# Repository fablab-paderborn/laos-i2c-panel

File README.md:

# laos-i2c-panel
This is an rebuild of the LAOS I2C Panel v0.4, optimized for single-sided assembly and cnc milled production.

The original pcb is published at
  https://github.com/LaosLaser/AddOns/tree/master/i2c-panel/pcb-0.4
and designed with KiCAD.

This version is redesigned with EAGLE and optimized for milled production.

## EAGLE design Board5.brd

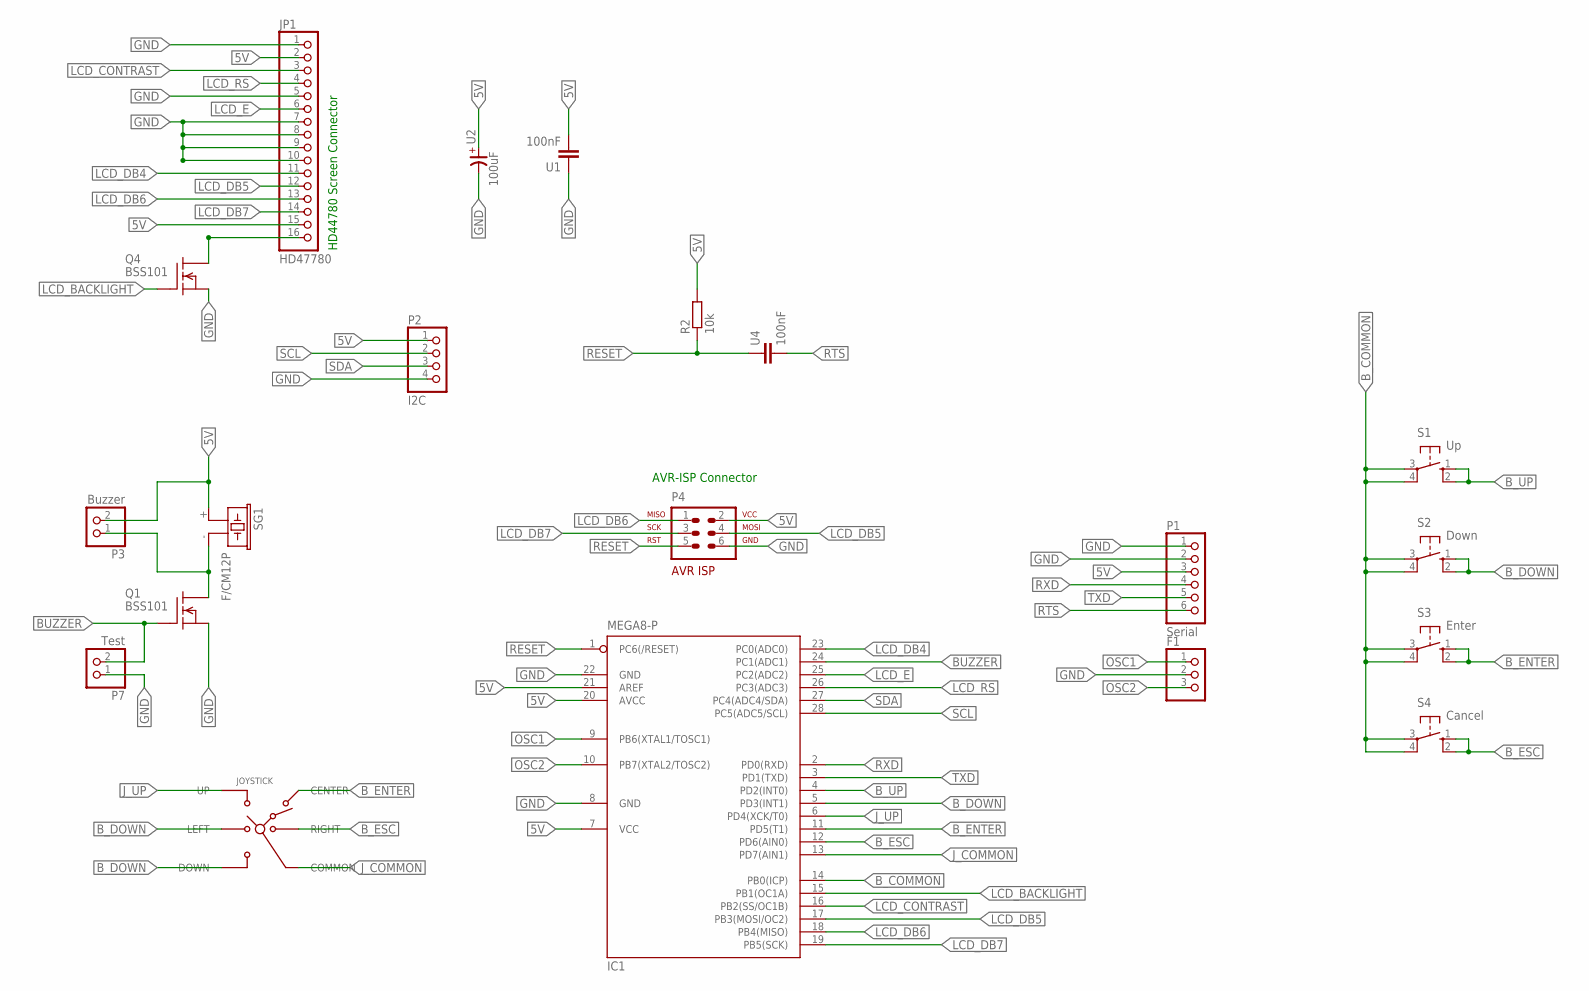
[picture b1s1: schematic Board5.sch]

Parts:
F1: PINHD-1X3; 1X03
IC1: MEGA8-P; DIL28-3
JOYSTICK: SKQUAAA010; SKQU
JP1: HD47780; 1X16
P1: Serial; 1X06
P2: I2C; 1X04
P3: Buzzer; 1X02
P4: ISP_WANNENBUCHSE; ML6
P7: Test; 1X02
Q1, Q4: BSS101; TO92
R2: 10k; 0207/10
S1: Up; B3F-40XX
S2: Down; B3F-40XX
S3: Enter; B3F-40XX
S4: Cancel; B3F-40XX
SG1: F/CM12P
U1, U4: 100nF; C050-024X044
U2: 100uF; E-020X050

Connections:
5V: IC1.7 (VCC), IC1.20 (AVCC), IC1.21 (AREF), JP1.2, JP1.15, P1.3, P2.1, P3.2, P4.2 (VCC), R2.2, SG1.+ (1), U1.2, U2.+
BUZZER: IC1.24 (PC1(ADC1)), P7.2, Q1.2 (G)
B_COMMON: IC1.14 (PB0(ICP)), S1.3, S1.4 (P1), S2.3, S2.4 (P1), S3.3, S3.4 (P1), S4.3, S4.4 (P1)
B_DOWN: IC1.5 (PD3(INT1)), JOYSTICK.DOWN, JOYSTICK.LEFT, S2.1 (S), S2.2 (S1)
B_ENTER: IC1.11 (PD5(T1)), JOYSTICK.CENTER, S3.1 (S), S3.2 (S1)
B_ESC: IC1.12 (PD6(AIN0)), JOYSTICK.RIGHT, S4.1 (S), S4.2 (S1)
B_UP: IC1.4 (PD2(INT0)), S1.1 (S), S1.2 (S1)
GND: F1.2, IC1.8 (GND), IC1.22 (GND), JP1.1, JP1.5, JP1.7, JP1.8, JP1.9, JP1.10, P1.1, P1.2, P2.4, P4.6 (GND), P7.1, Q1.1 (S), Q4.1 (S), U1.1, U2.-
J_COMMON: IC1.13 (PD7(AIN1)), JOYSTICK.COMMON
J_UP: IC1.6 (PD4(XCK/T0)), JOYSTICK.UP
LCD_BACKLIGHT: IC1.15 (PB1(OC1A)), Q4.2 (G)
LCD_CONTRAST: IC1.16 (PB2(SS/OC1B)), JP1.3
LCD_DB4: IC1.23 (PC0(ADC0)), JP1.11
LCD_DB5: IC1.17 (PB3(MOSI/OC2)), JP1.12, P4.4 (MOSI)
LCD_DB6: IC1.18 (PB4(MISO)), JP1.13, P4.1 (MISO)
LCD_DB7: IC1.19 (PB5(SCK)), JP1.14, P4.3 (SCK)
LCD_E: IC1.25 (PC2(ADC2)), JP1.6
LCD_RS: IC1.26 (PC3(ADC3)), JP1.4
unnamed: JP1.16, Q4.3 (D)
unnamed: P3.1, Q1.3 (D), SG1.- (2)
OSC1: F1.1, IC1.9 (PB6(XTAL1/TOSC1))
OSC2: F1.3, IC1.10 (PB7(XTAL2/TOSC2))
RESET: IC1.1 (PC6(/RESET)), P4.5 (RST), R2.1, U4.1
RTS: P1.6, U4.2
RXD: IC1.2 (PD0(RXD)), P1.4
SCL: IC1.28 (PC5(ADC5/SCL)), P2.2
SDA: IC1.27 (PC4(ADC4/SDA)), P2.3
TXD: IC1.3 (PD1(TXD)), P1.5

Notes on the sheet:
AVR-ISP Connector
HD44780 Screen Connector

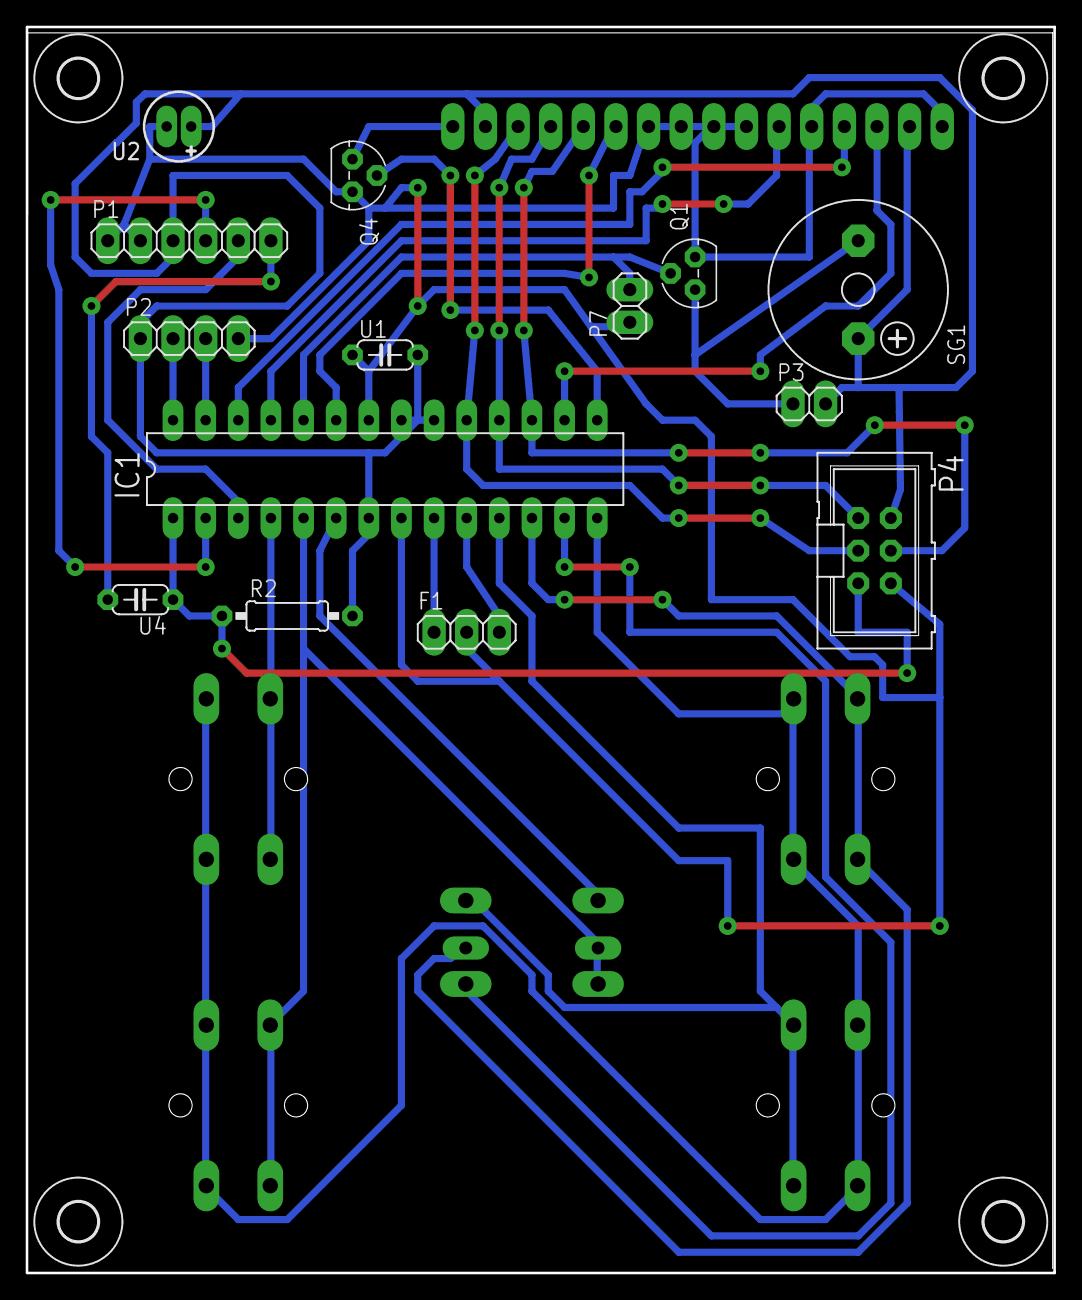
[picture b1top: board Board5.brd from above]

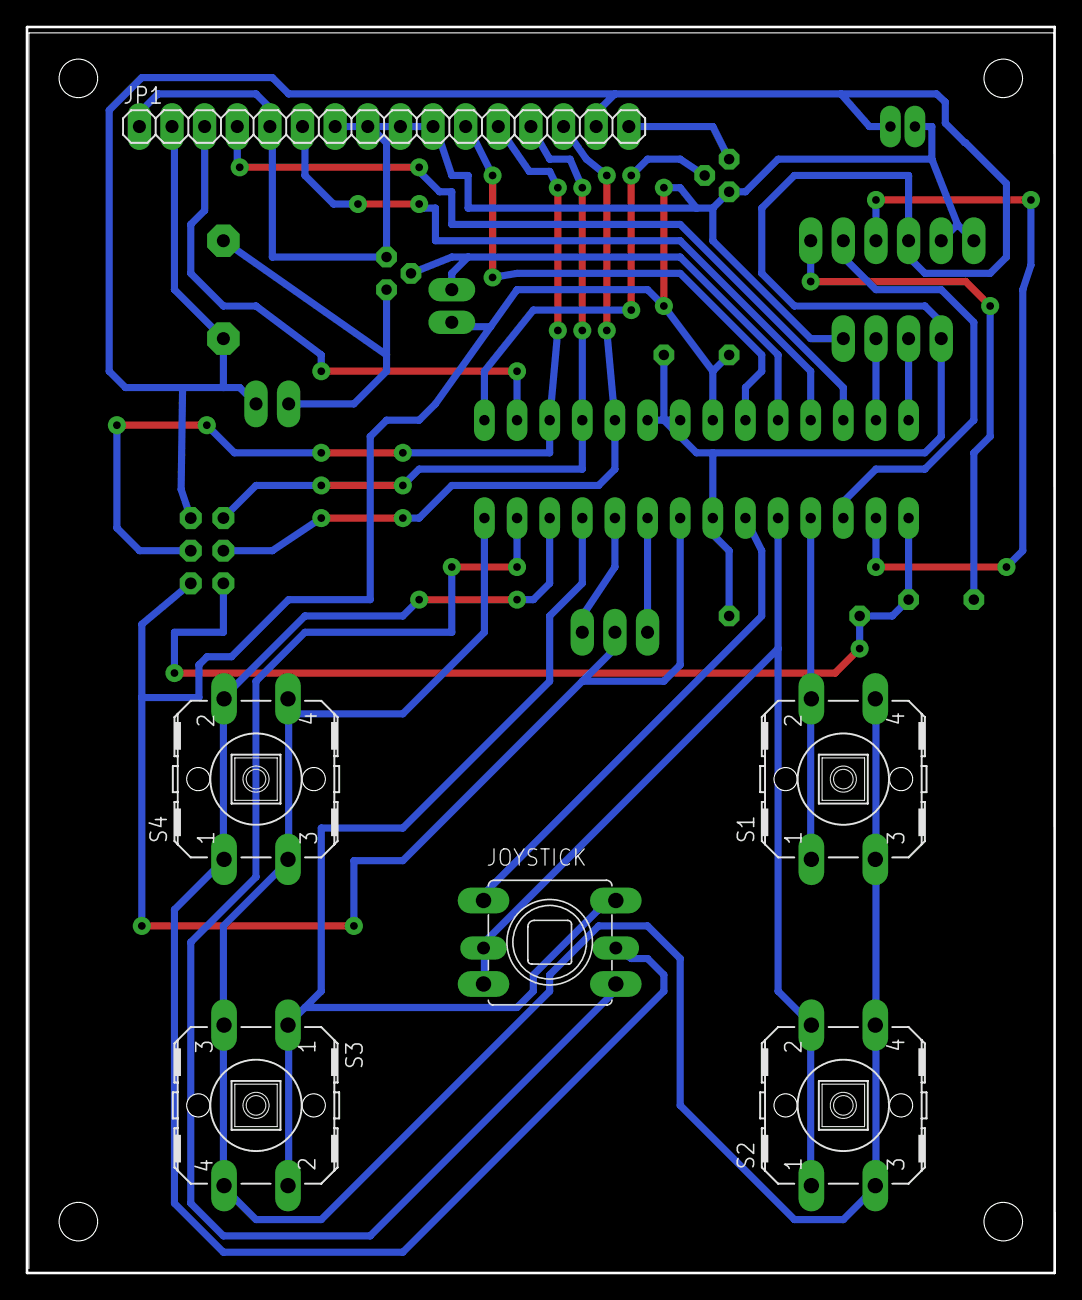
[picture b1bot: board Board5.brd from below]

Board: 2 copper layers, 80.0 x 97.0 mm, 24 parts (6 on the bottom side), 28 nets.

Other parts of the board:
U$1, U$2, U$3, U$4: 3,0

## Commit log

2015-05-18 Revision I
2015-05-28 new gcode files
2015-05-28 new revision with 16 mil clearance instead of 12 mil
2015-05-28 bug in pcb fixed
2015-05-28 Top Print
2015-07-14 Board5: Extended Width
2015-07-15 Mirrored and with Holes in the Pads
